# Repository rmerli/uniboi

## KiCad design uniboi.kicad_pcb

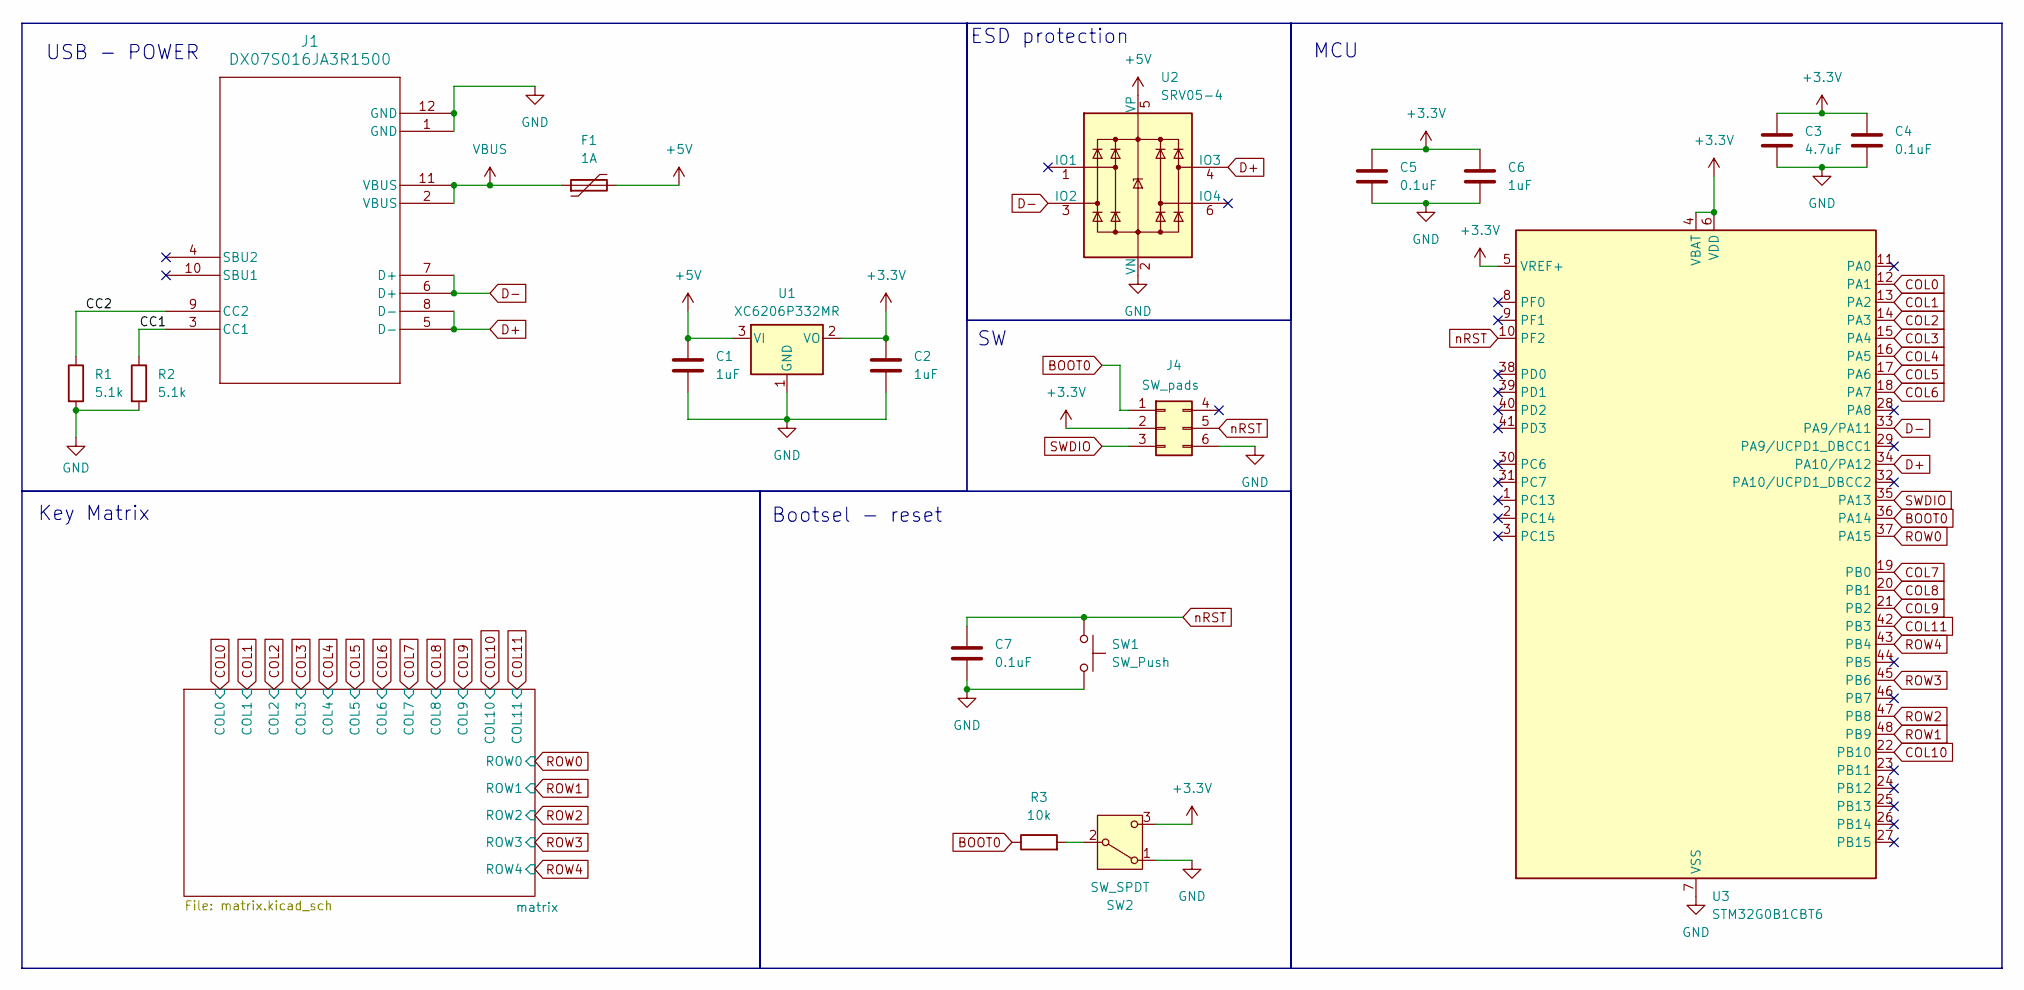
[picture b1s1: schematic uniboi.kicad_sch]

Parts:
C1, C2, C6: 1uF; C_0402_1005Metric
C3: 4.7uF; C_0402_1005Metric
C4, C5, C7: 0.1uF; C_0402_1005Metric
F1: 1A; Fuse_1206_3216Metric
J1: DX07S016JA3R1500; CONN12_DX07S_JAE_no_edge_cuts
J4: SW_pads; Tag-Connect_TC2030-IDC-NL_2x03_P1.27mm_Vertical
R1, R2: 5.1k; R_0402_1005Metric
R3: 10k; R_0402_1005Metric
SW1: SW_Push; SW_SPST_TS-1088-xR020
SW2: SW_SPDT; SW_SPDT_PCM12
U1: XC6206P332MR; SOT-23-3
U2: SRV05-4; SOT-23-6
U3: STM32G0B1CBT6; LQFP-48_7x7mm_P0.5mm

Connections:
+3.3V: C2.1, C3.1, C4.1, C5.1, C6.1, J4.2, SW2.3 (C), U1.2 (VO), U3.4 (VBAT), U3.5 (VREF+), U3.6 (VDD)
+5V: C1.1, F1.2, U1.3 (VI), U2.5 (VP)
/CC1: J1.3 (CC1), R2.1
/CC2: J1.9 (CC2), R1.1
BOOT0: J4.1, R3.1, U3.36 (PA14)
COL0: U3.12 (PA1); also elsewhere on the board
COL1: U3.13 (PA2); also elsewhere on the board
COL2: U3.14 (PA3); also elsewhere on the board
COL3: U3.15 (PA4); also elsewhere on the board
COL4: U3.16 (PA5); also elsewhere on the board
COL5: U3.17 (PA6); also elsewhere on the board
COL6: U3.18 (PA7); also elsewhere on the board
COL7: U3.19 (PB0); also elsewhere on the board
COL8: U3.20 (PB1); also elsewhere on the board
COL9: U3.21 (PB2); also elsewhere on the board
COL10: U3.22 (PB10); also elsewhere on the board
COL11: U3.42 (PB3); also elsewhere on the board
D+: J1.5 (D-), J1.8 (D-), U2.4 (IO3), U3.34 (PA10/PA12)
D-: J1.6 (D+), J1.7 (D+), U2.3 (IO2), U3.33 (PA9/PA11)
GND: C1.2, C2.2, C3.2, C4.2, C5.2, C6.2, C7.2, J1.1 (GND), J1.12 (GND), J4.6, R1.2, R2.2, SW1.2, SW2.1 (A), U1.1 (GND), U2.2 (VN), U3.7 (VSS)
unnamed: R3.2, SW2.2 (B)
ROW0: U3.37 (PA15); also elsewhere on the board
ROW1: U3.48 (PB9); also elsewhere on the board
ROW2: U3.47 (PB8); also elsewhere on the board
ROW3: U3.45 (PB6); also elsewhere on the board
ROW4: U3.43 (PB4); also elsewhere on the board
SWDIO: J4.3, U3.35 (PA13)
VBUS: F1.1, J1.2 (VBUS), J1.11 (VBUS)
nRST: C7.1, J4.5, SW1.1, U3.10 (PF2)

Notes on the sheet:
MCU
Bootsel - reset
Key Matrix
ESD protection
USB - POWER

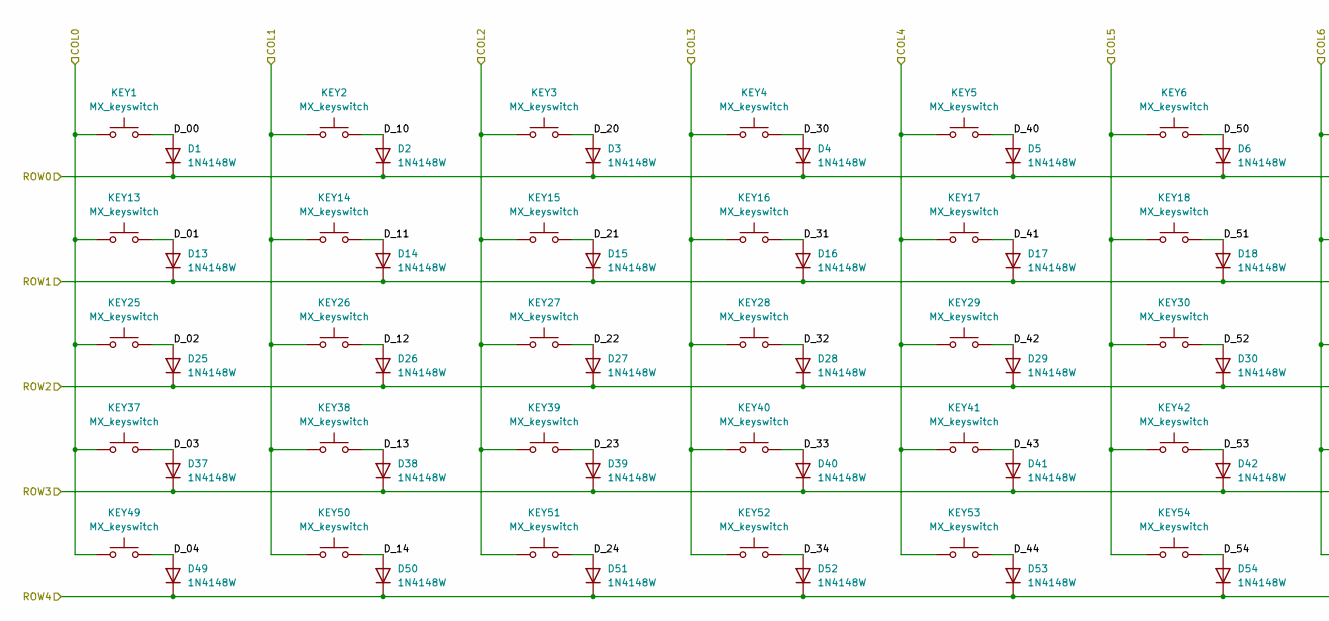
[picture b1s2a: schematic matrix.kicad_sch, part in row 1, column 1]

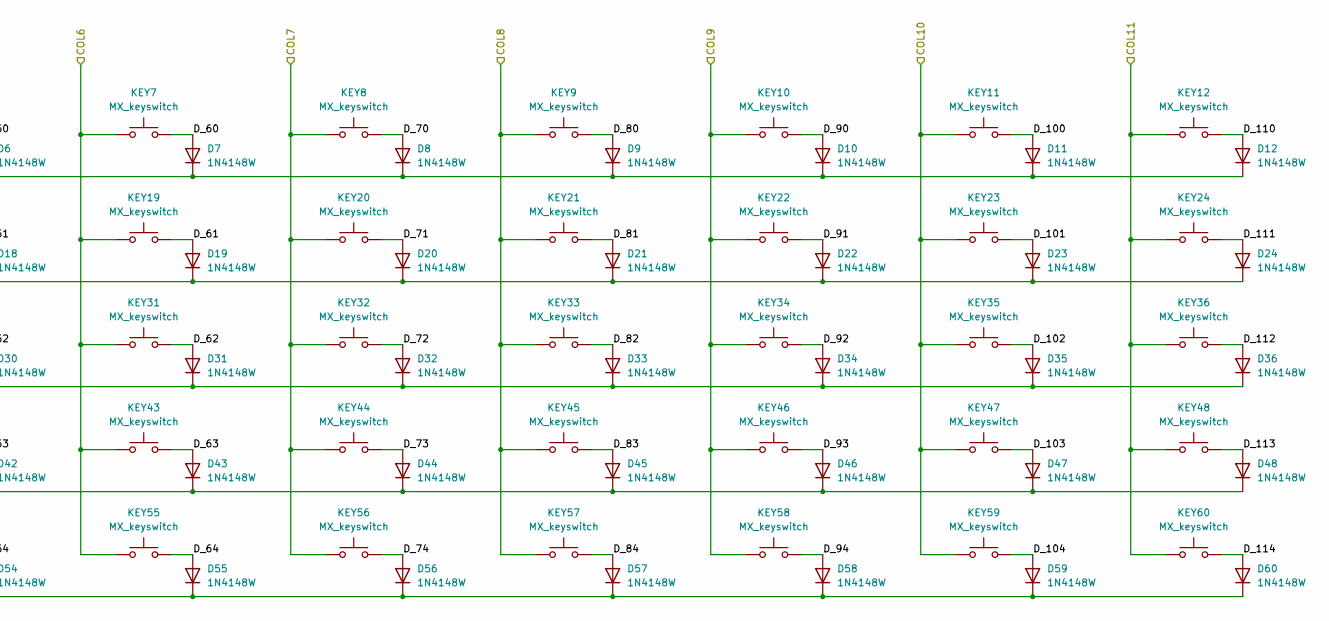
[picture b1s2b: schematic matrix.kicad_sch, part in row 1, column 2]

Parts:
D1, D2, D3, D4, D5, D6, D7, D8, D9, D10, D11, D12, D13, D14, D15, D16, D17, D18, D19, D20, D21, D22, D23, D24, D25, D26, D27, D28, D29, D30, D31, D32, D33, D34, D35, D36, D37, D38, D39, D40, D41, D42, D43, D44, D45, D46, D47, D48, D49, D50, D51, D52, D53, D54, D55, D56, D57, D58, D59, D60: 1N4148W; D_SOD-123
KEY1, KEY2, KEY3, KEY4, KEY5, KEY6, KEY7, KEY8, KEY9, KEY10, KEY11, KEY12, KEY13, KEY14, KEY15, KEY16, KEY17, KEY18, KEY19, KEY20, KEY21, KEY22, KEY23, KEY24, KEY25, KEY26, KEY27, KEY28, KEY29, KEY30, KEY31, KEY32, KEY33, KEY34, KEY35, KEY36, KEY37, KEY38, KEY39, KEY40, KEY41, KEY42, KEY43, KEY44, KEY45, KEY46, KEY47, KEY48, KEY49, KEY50, KEY51, KEY52, KEY53, KEY54, KEY55, KEY56, KEY57, KEY58, KEY59, KEY60: MX_keyswitch; MX-Hotswap-1U

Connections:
/matrix/ D_92: D34.2 (A), KEY34.2
/matrix/ D_102: D35.2 (A), KEY35.2
/matrix/ D_112: D36.2 (A), KEY36.2
/matrix/D_00: D1.2 (A), KEY1.2
/matrix/D_01: D13.2 (A), KEY13.2
/matrix/D_02: D25.2 (A), KEY25.2
/matrix/D_03: D37.2 (A), KEY37.2
/matrix/D_04: D49.2 (A), KEY49.2
/matrix/D_10: D2.2 (A), KEY2.2
/matrix/D_11: D14.2 (A), KEY14.2
/matrix/D_12: D26.2 (A), KEY26.2
/matrix/D_13: D38.2 (A), KEY38.2
/matrix/D_14: D50.2 (A), KEY50.2
/matrix/D_20: D3.2 (A), KEY3.2
/matrix/D_21: D15.2 (A), KEY15.2
/matrix/D_22: D27.2 (A), KEY27.2
/matrix/D_23: D39.2 (A), KEY39.2
/matrix/D_24: D51.2 (A), KEY51.2
/matrix/D_30: D4.2 (A), KEY4.2
/matrix/D_31: D16.2 (A), KEY16.2
/matrix/D_32: D28.2 (A), KEY28.2
/matrix/D_33: D40.2 (A), KEY40.2
/matrix/D_34: D52.2 (A), KEY52.2
/matrix/D_40: D5.2 (A), KEY5.2
/matrix/D_41: D17.2 (A), KEY17.2
/matrix/D_42: D29.2 (A), KEY29.2
/matrix/D_43: D41.2 (A), KEY41.2
/matrix/D_44: D53.2 (A), KEY53.2
/matrix/D_50: D6.2 (A), KEY6.2
/matrix/D_51: D18.2 (A), KEY18.2
/matrix/D_52: D30.2 (A), KEY30.2
/matrix/D_53: D42.2 (A), KEY42.2
/matrix/D_54: D54.2 (A), KEY54.2
/matrix/D_60: D7.2 (A), KEY7.2
/matrix/D_61: D19.2 (A), KEY19.2
/matrix/D_62: D31.2 (A), KEY31.2
/matrix/D_63: D43.2 (A), KEY43.2
/matrix/D_64: D55.2 (A), KEY55.2
/matrix/D_70: D8.2 (A), KEY8.2
/matrix/D_71: D20.2 (A), KEY20.2
/matrix/D_72: D32.2 (A), KEY32.2
/matrix/D_73: D44.2 (A), KEY44.2
/matrix/D_74: D56.2 (A), KEY56.2
/matrix/D_80: D9.2 (A), KEY9.2
/matrix/D_81: D21.2 (A), KEY21.2
/matrix/D_82: D33.2 (A), KEY33.2
/matrix/D_83: D45.2 (A), KEY45.2
/matrix/D_84: D57.2 (A), KEY57.2
/matrix/D_90: D10.2 (A), KEY10.2
/matrix/D_91: D22.2 (A), KEY22.2
/matrix/D_93: D46.2 (A), KEY46.2
/matrix/D_94: D58.2 (A), KEY58.2
/matrix/D_100: D11.2 (A), KEY11.2
/matrix/D_101: D23.2 (A), KEY23.2
/matrix/D_103: D47.2 (A), KEY47.2
/matrix/D_104: D59.2 (A), KEY59.2
/matrix/D_110: D12.2 (A), KEY12.2
/matrix/D_111: D24.2 (A), KEY24.2
/matrix/D_113: D48.2 (A), KEY48.2
/matrix/D_114: D60.2 (A), KEY60.2
COL0: KEY1.1, KEY13.1, KEY25.1, KEY37.1, KEY49.1; also elsewhere on the board
COL1: KEY2.1, KEY14.1, KEY26.1, KEY38.1, KEY50.1; also elsewhere on the board
COL2: KEY3.1, KEY15.1, KEY27.1, KEY39.1, KEY51.1; also elsewhere on the board
COL3: KEY4.1, KEY16.1, KEY28.1, KEY40.1, KEY52.1; also elsewhere on the board
COL4: KEY5.1, KEY17.1, KEY29.1, KEY41.1, KEY53.1; also elsewhere on the board
COL5: KEY6.1, KEY18.1, KEY30.1, KEY42.1, KEY54.1; also elsewhere on the board
COL6: KEY7.1, KEY19.1, KEY31.1, KEY43.1, KEY55.1; also elsewhere on the board
COL7: KEY8.1, KEY20.1, KEY32.1, KEY44.1, KEY56.1; also elsewhere on the board
COL8: KEY9.1, KEY21.1, KEY33.1, KEY45.1, KEY57.1; also elsewhere on the board
COL9: KEY10.1, KEY22.1, KEY34.1, KEY46.1, KEY58.1; also elsewhere on the board
COL10: KEY11.1, KEY23.1, KEY35.1, KEY47.1, KEY59.1; also elsewhere on the board
COL11: KEY12.1, KEY24.1, KEY36.1, KEY48.1, KEY60.1; also elsewhere on the board
ROW0: D1.1 (K), D2.1 (K), D3.1 (K), D4.1 (K), D5.1 (K), D6.1 (K), D7.1 (K), D8.1 (K), D9.1 (K), D10.1 (K), D11.1 (K), D12.1 (K); also elsewhere on the board
ROW1: D13.1 (K), D14.1 (K), D15.1 (K), D16.1 (K), D17.1 (K), D18.1 (K), D19.1 (K), D20.1 (K), D21.1 (K), D22.1 (K), D23.1 (K), D24.1 (K); also elsewhere on the board
ROW2: D25.1 (K), D26.1 (K), D27.1 (K), D28.1 (K), D29.1 (K), D30.1 (K), D31.1 (K), D32.1 (K), D33.1 (K), D34.1 (K), D35.1 (K), D36.1 (K); also elsewhere on the board
ROW3: D37.1 (K), D38.1 (K), D39.1 (K), D40.1 (K), D41.1 (K), D42.1 (K), D43.1 (K), D44.1 (K), D45.1 (K), D46.1 (K), D47.1 (K), D48.1 (K); also elsewhere on the board
ROW4: D49.1 (K), D50.1 (K), D51.1 (K), D52.1 (K), D53.1 (K), D54.1 (K), D55.1 (K), D56.1 (K), D57.1 (K), D58.1 (K), D59.1 (K), D60.1 (K); also elsewhere on the board

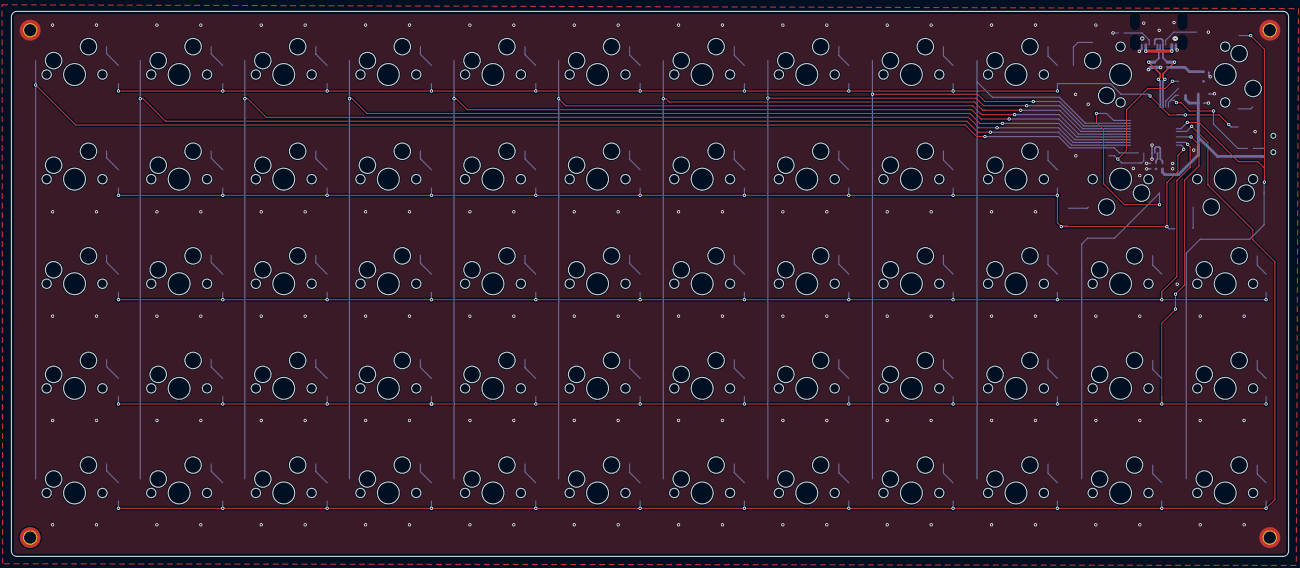
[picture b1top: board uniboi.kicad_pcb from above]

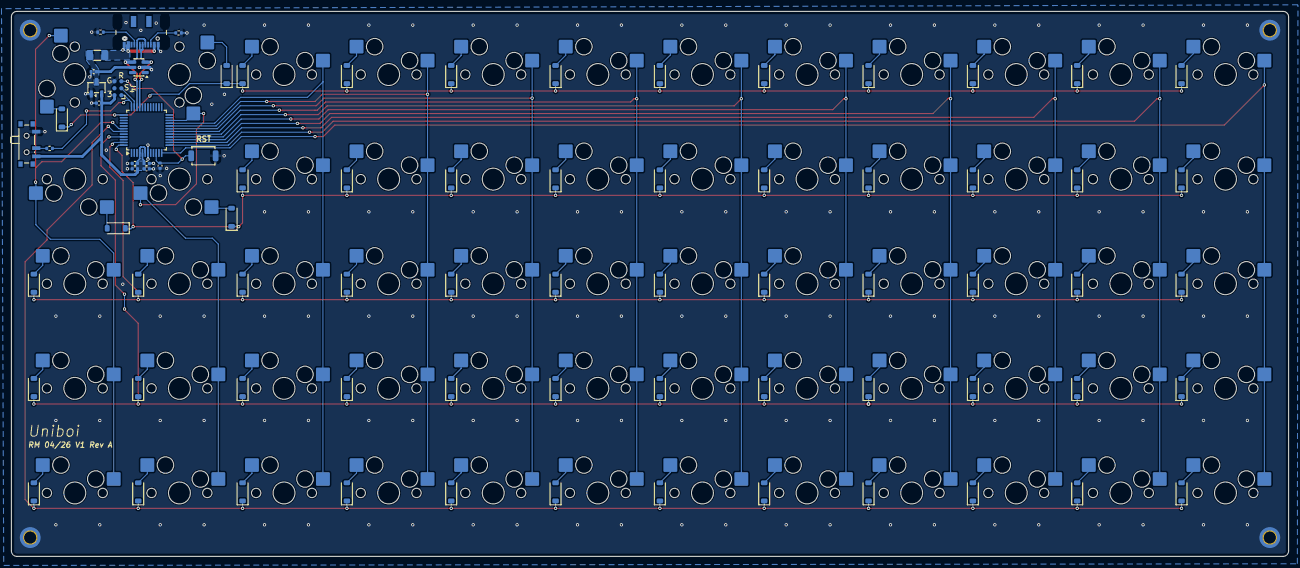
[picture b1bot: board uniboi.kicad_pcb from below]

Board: 2 copper layers, 232.6 x 99.2 mm, 138 parts (138 on the bottom side), 89 nets.

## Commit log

2026-04-04 init
2026-04-04 WIP: first draft of schematics
2026-04-04 added keyswitch footprint submodule
2026-04-04 WIP: footprints
2026-04-04 cleanup
2026-04-05 WIP:routing
2026-04-05 WIP: changed usb-c connector, updated schematics with the SRV05-4, updated routing
2026-04-06 WIP: schematics and routing
2026-04-06 WIP: routed matrix and added swdio
2026-04-07 WIP: updated usb VBUS route
2026-04-09 clean up and final touches
2026-04-10 v0.1
